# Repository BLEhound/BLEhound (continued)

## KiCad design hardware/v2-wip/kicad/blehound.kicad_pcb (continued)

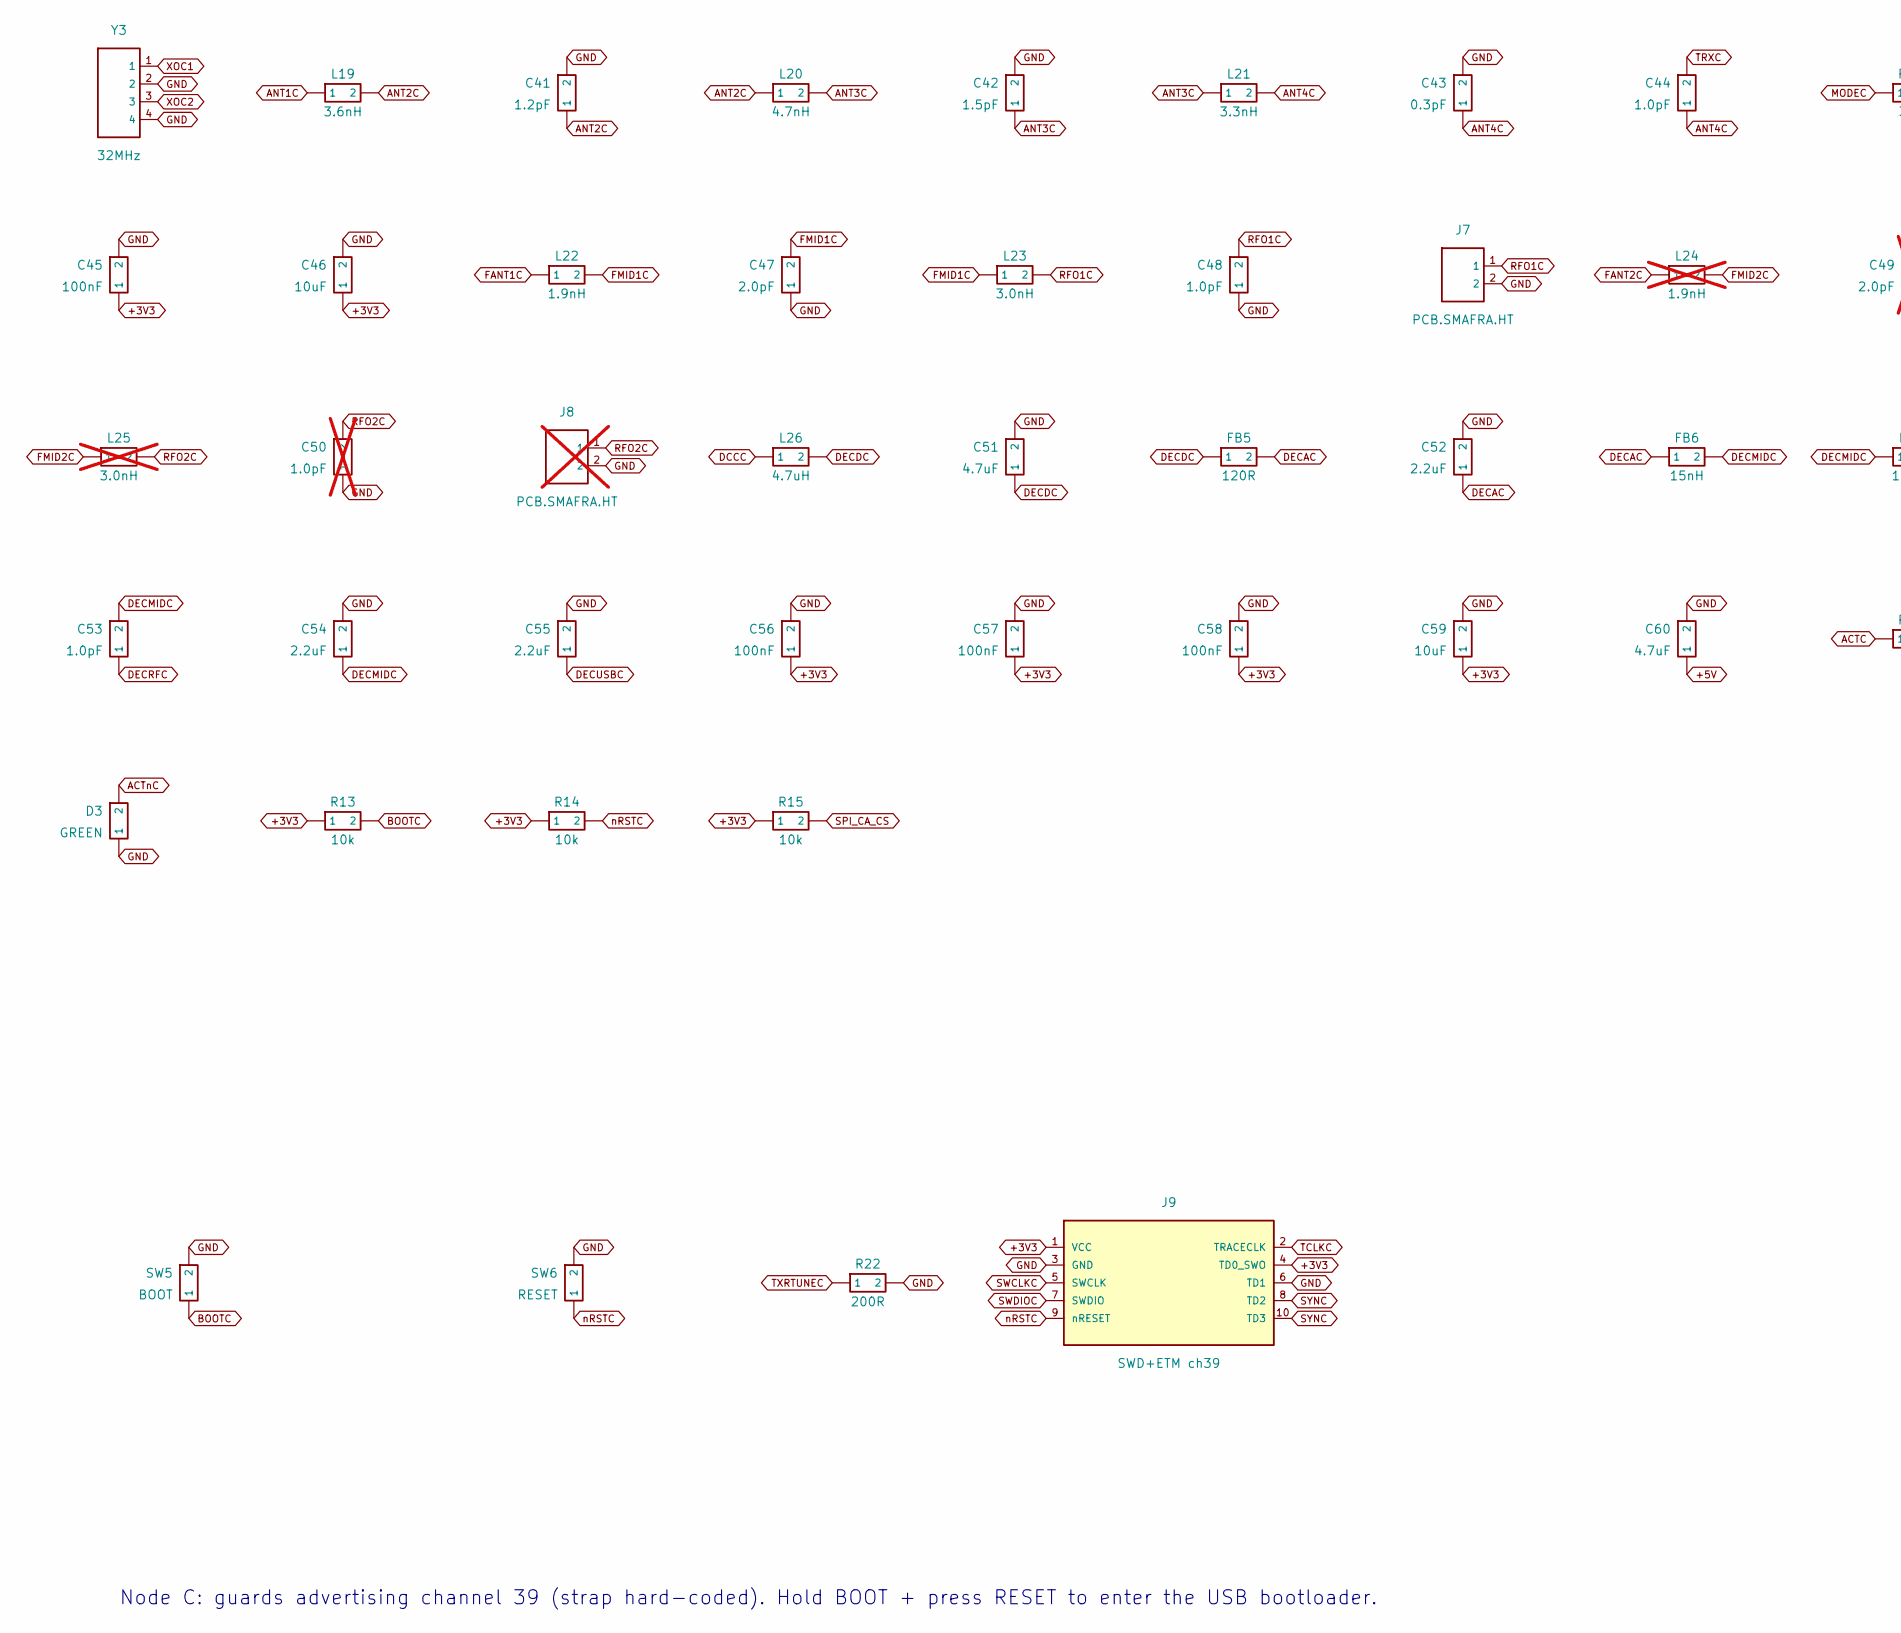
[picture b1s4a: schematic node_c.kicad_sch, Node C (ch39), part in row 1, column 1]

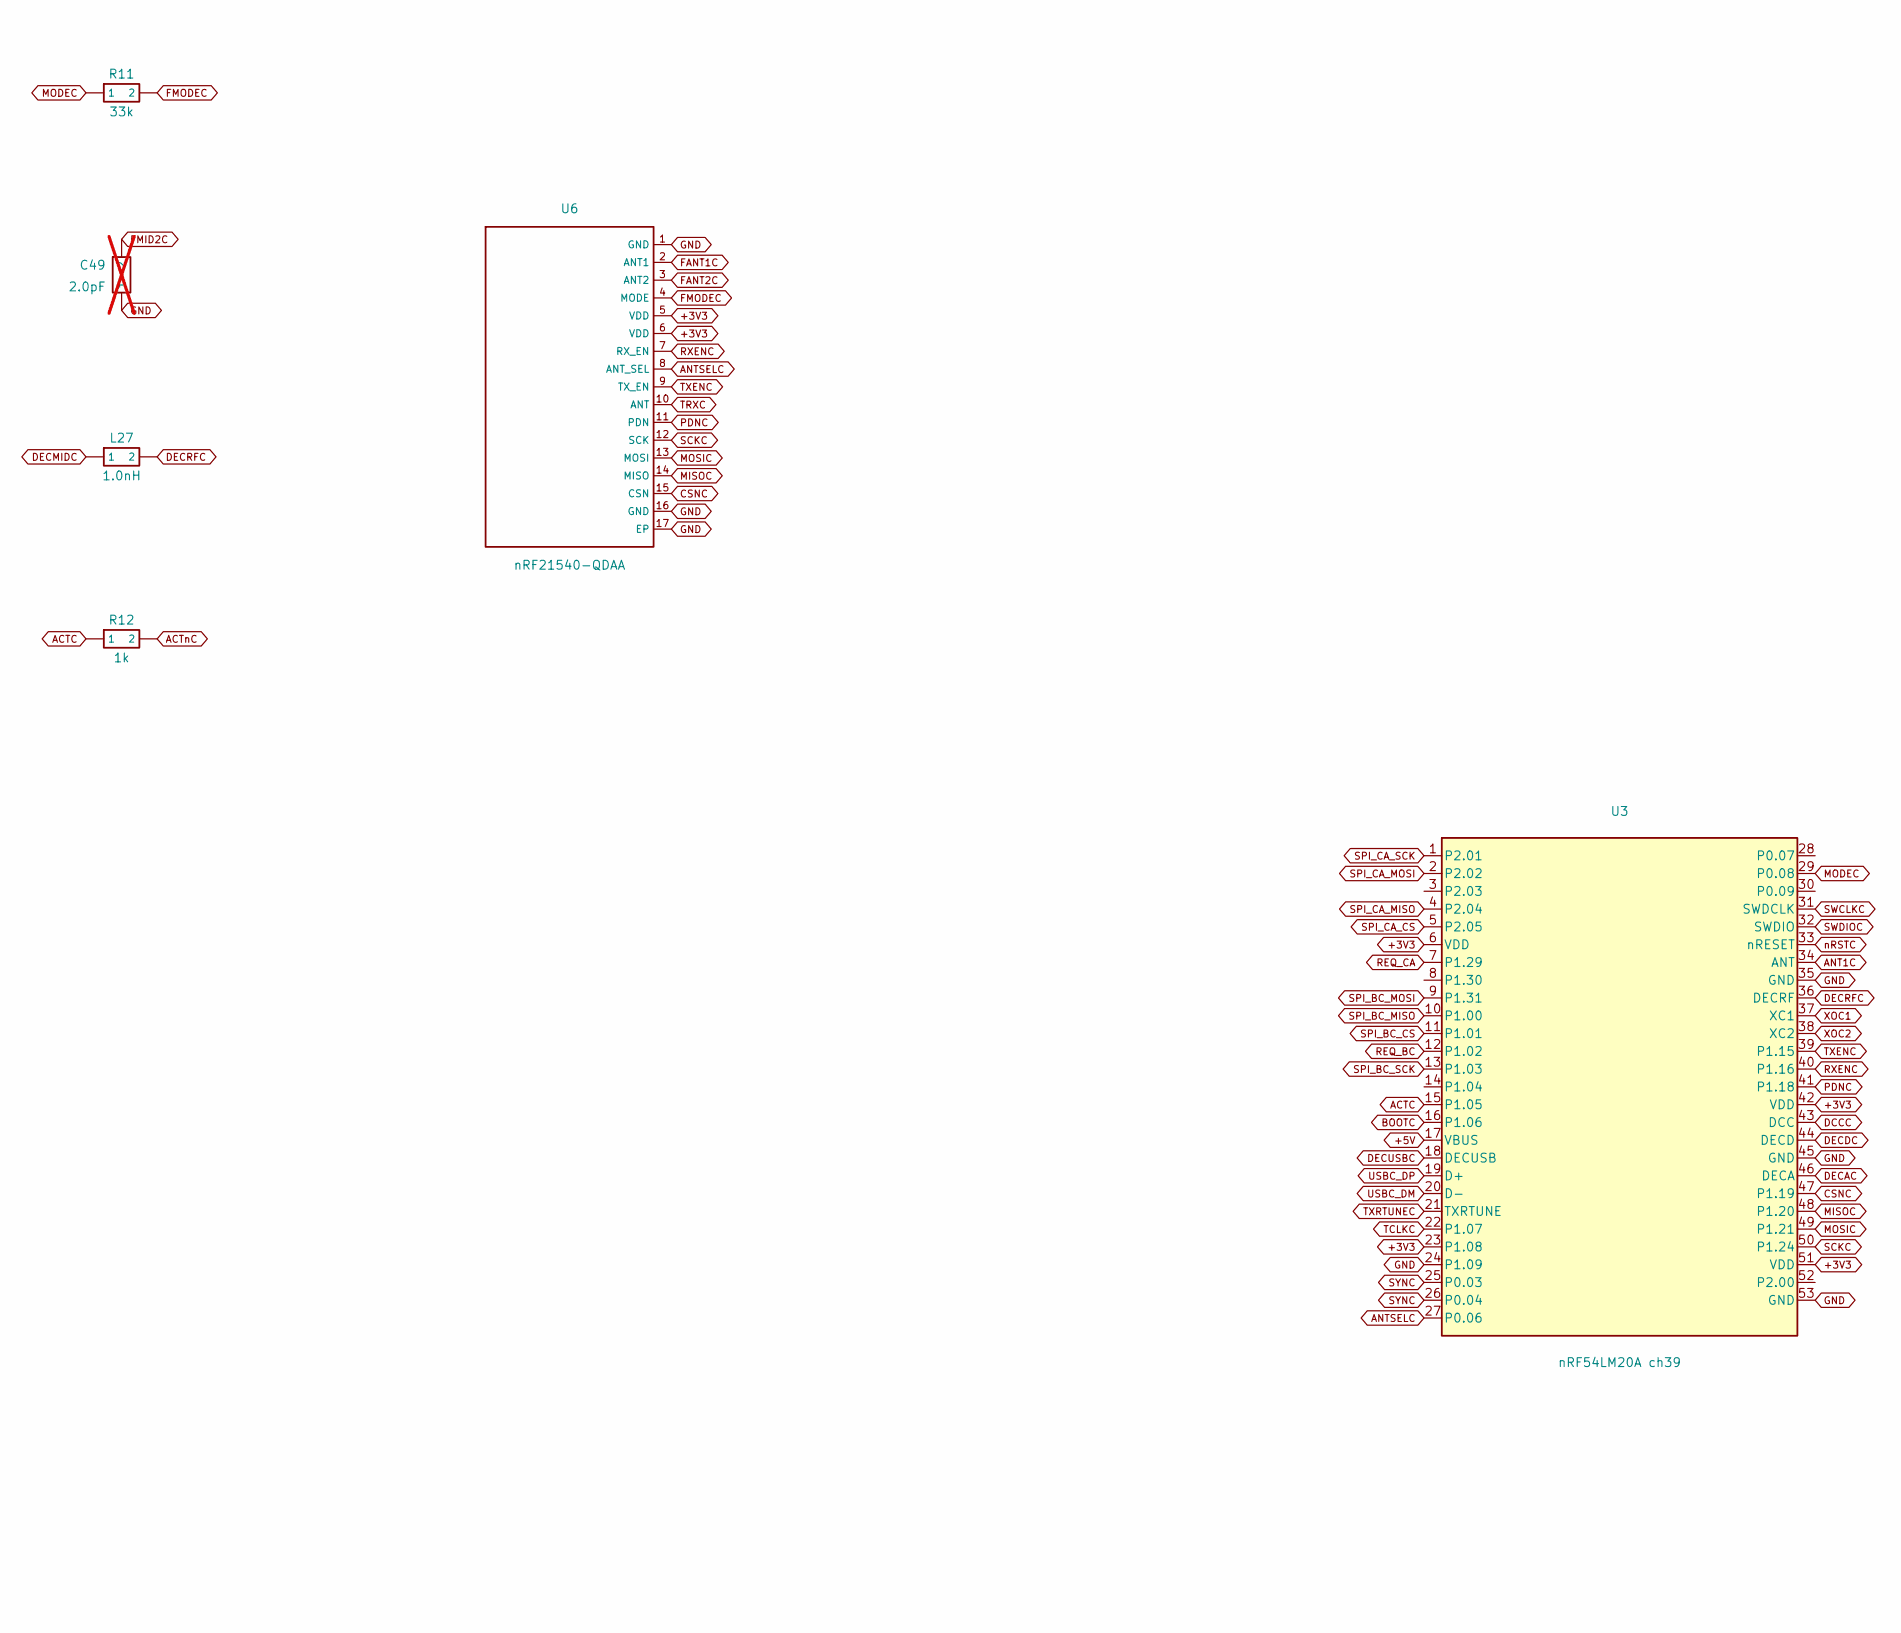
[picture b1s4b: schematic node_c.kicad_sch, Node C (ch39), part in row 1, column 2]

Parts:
C41: 1.2pF; DK_C_0201_0603Metric
C42: 1.5pF; DK_C_0201_0603Metric
C43: 0.3pF; DK_C_0201_0603Metric
C44, C48, C53: 1.0pF; DK_C_0201_0603Metric
C45: 100nF; DK_C_0201_0603Metric
C46: 10uF; DK_C_0603_1608Metric
C47: 2.0pF; DK_C_0201_0603Metric
C49: 2.0pF; DK_C_0201_0603Metric; not fitted
C50: 1.0pF; DK_C_0201_0603Metric; not fitted
C51: 4.7uF; DK_C_0201_0603Metric
C52, C54, C55: 2.2uF; DK_C_0201_0603Metric
C56, C57, C58: 100nF; C_0402_1005Metric
C59: 10uF; C_0603_1608Metric
C60: 4.7uF; C_0603_1608Metric
D3: GREEN; LED_0603_1608Metric
FB5: 120R; DK_L_0201_0603Metric
FB6: 15nH; DK_L_0201_0603Metric
J7: PCB.SMAFRA.HT; SMA_RA_TH_PCBSMAFRA_HT
J8: PCB.SMAFRA.HT; SMA_RA_TH_PCBSMAFRA_HT; not fitted
J9: SWD+ETM ch39; PinHeader_2x05_P2.54mm_Vertical
L19: 3.6nH; DK_L_0201_0603Metric
L20: 4.7nH; DK_L_0201_0603Metric
L21: 3.3nH; DK_L_0201_0603Metric
L22: 1.9nH; DK_L_0201_0603Metric
L23: 3.0nH; DK_L_0201_0603Metric
L24: 1.9nH; DK_L_0201_0603Metric; not fitted
L25: 3.0nH; DK_L_0201_0603Metric; not fitted
L26: 4.7uH; DK_L_0603_1608Metric
L27: 1.0nH; DK_L_0201_0603Metric
R11: 33k; DK_R_0201_0603Metric
R12: 1k; R_0402_1005Metric
R13, R14, R15: 10k; R_0402_1005Metric
R22: 200R; R_0402_1005Metric
SW5: BOOT; SW_SPST_SKQG_WithoutStem
SW6: RESET; SW_SPST_SKQG_WithoutStem
U3: nRF54LM20A ch39; nRF54LM20A_QFN52_6x6mm_P0.4mm_EP4.7x4.7mm
U6: nRF21540-QDAA; nRF21540_QFN16_4x4mm_P0.65mm_EP2.65
Y3: 32MHz; DK_Crystal_32MHz

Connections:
+3V3: C45.1, C46.1, C56.1, C57.1, C58.1, C59.1, J9.1 (VCC), J9.4 (TD0_SWO), R13.1, R14.1, R15.1, U3.6 (VDD), U3.23 (P1.08), U3.42 (VDD), U3.51 (VDD), U6.5 (VDD), U6.6 (VDD); also elsewhere on the board
+5V: C60.1, U3.17 (VBUS); also elsewhere on the board
ACTC: R12.1, U3.15 (P1.05)
ACTnC: D3.2, R12.2
ANT1C: L19.1, U3.34 (ANT)
ANT2C: C41.1, L19.2, L20.1
ANT3C: C42.1, L20.2, L21.1
ANT4C: C43.1, C44.1, L21.2
ANTSELC: U3.27 (P0.06), U6.8 (ANT_SEL)
BOOTC: R13.2, SW5.1, U3.16 (P1.06)
CSNC: U3.47 (P1.19), U6.15 (CSN)
DCCC: L26.1, U3.43 (DCC)
DECAC: C52.1, FB5.2, FB6.1, U3.46 (DECA)
DECDC: C51.1, FB5.1, L26.2, U3.44 (DECD)
DECMIDC: C53.2, C54.1, FB6.2, L27.1
DECRFC: C53.1, L27.2, U3.36 (DECRF)
DECUSBC: C55.1, U3.18 (DECUSB)
FANT1C: L22.1, U6.2 (ANT1)
FANT2C: L24.1, U6.3 (ANT2)
FMID1C: C47.2, L22.2, L23.1
FMID2C: C49.2, L24.2, L25.1
FMODEC: R11.2, U6.4 (MODE)
GND: C41.2, C42.2, C43.2, C45.2, C46.2, C47.1, C48.1, C49.1, C50.1, C51.2, C52.2, C54.2, C55.2, C56.2, C57.2, C58.2, C59.2, C60.2, D3.1, J7.2, J8.2, J9.3 (GND), J9.6 (TD1), R22.2, SW5.2, SW6.2, U3.24 (P1.09), U3.35 (GND), U3.45 (GND), U3.53 (GND), U6.1 (GND), U6.16 (GND), U6.17 (EP), Y3.2, Y3.4; also elsewhere on the board
MISOC: U3.48 (P1.20), U6.14 (MISO)
MODEC: R11.1, U3.29 (P0.08)
MOSIC: U3.49 (P1.21), U6.13 (MOSI)
PDNC: U3.41 (P1.18), U6.11 (PDN)
REQ_BC: U3.12 (P1.02); also elsewhere on the board
REQ_CA: U3.7 (P1.29); also elsewhere on the board
RFO1C: C48.2, J7.1, L23.2
RFO2C: C50.2, J8.1, L25.2
RXENC: U3.40 (P1.16), U6.7 (RX_EN)
SCKC: U3.50 (P1.24), U6.12 (SCK)
SPI_BC_CS: U3.11 (P1.01); also elsewhere on the board
SPI_BC_MISO: U3.10 (P1.00); also elsewhere on the board
SPI_BC_MOSI: U3.9 (P1.31); also elsewhere on the board
SPI_BC_SCK: U3.13 (P1.03); also elsewhere on the board
SPI_CA_CS: R15.2, U3.5 (P2.05); also elsewhere on the board
SPI_CA_MISO: U3.4 (P2.04); also elsewhere on the board
SPI_CA_MOSI: U3.2 (P2.02); also elsewhere on the board
SPI_CA_SCK: U3.1 (P2.01); also elsewhere on the board
SWCLKC: J9.5 (SWCLK), U3.31 (SWDCLK)
SWDIOC: J9.7 (SWDIO), U3.32 (SWDIO)
SYNC: J9.8 (TD2), J9.10 (TD3), U3.25 (P0.03), U3.26 (P0.04); also elsewhere on the board
TCLKC: J9.2 (TRACECLK), U3.22 (P1.07)
TRXC: C44.2, U6.10 (ANT)
TXENC: U3.39 (P1.15), U6.9 (TX_EN)
TXRTUNEC: R22.1, U3.21 (TXRTUNE)
USBC_DM: U3.20 (D-); also elsewhere on the board
USBC_DP: U3.19 (D+); also elsewhere on the board
XOC1: U3.37 (XC1), Y3.1
XOC2: U3.38 (XC2), Y3.3
nRSTC: J9.9 (nRESET), R14.2, SW6.1, U3.33 (nRESET)

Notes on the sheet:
Node C: guards advertising channel 39 (strap hard-coded). Hold BOOT + press RESET to enter the USB bootloader.

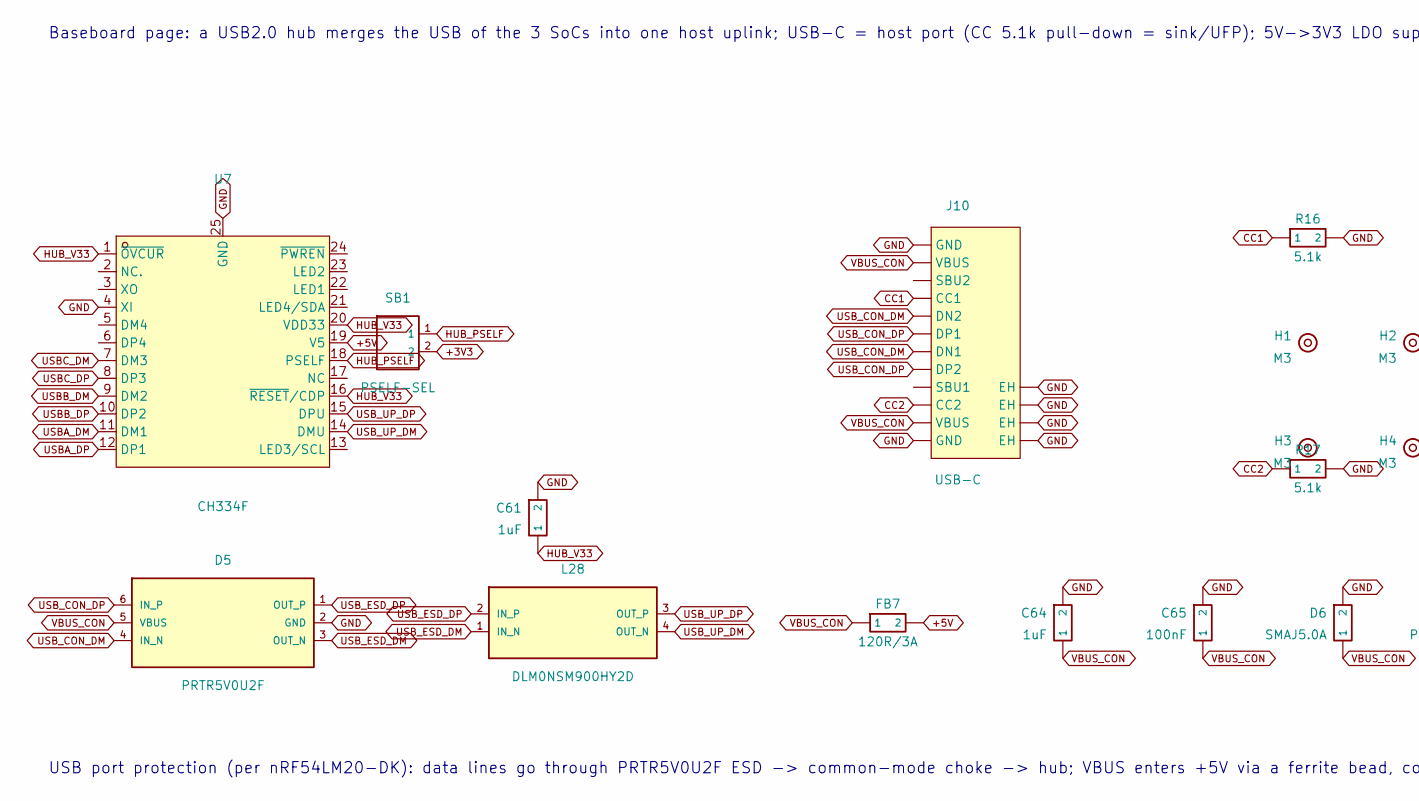
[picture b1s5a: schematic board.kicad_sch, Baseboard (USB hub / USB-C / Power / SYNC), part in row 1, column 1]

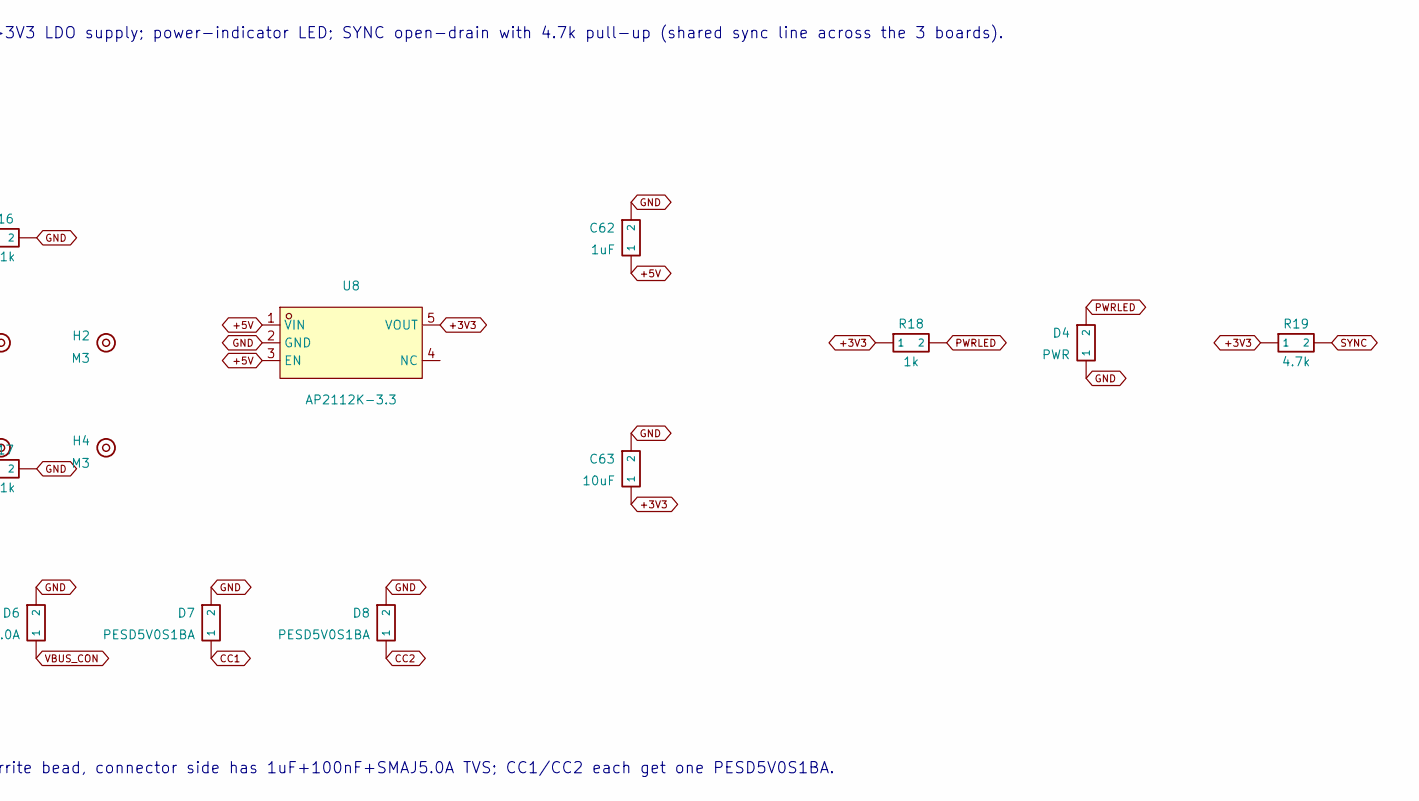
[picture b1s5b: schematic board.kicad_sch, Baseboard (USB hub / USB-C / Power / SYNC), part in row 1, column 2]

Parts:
C61: 1uF; C_0402_1005Metric
C62, C64: 1uF; C_0603_1608Metric
C63: 10uF; C_0603_1608Metric
C65: 100nF; C_0402_1005Metric
D4: PWR; LED_0603_1608Metric
D5: PRTR5V0U2F; SON50P100X50-6N
D6: SMAJ5.0A; D_SMA
D7, D8: PESD5V0S1BA; D_SOD-323
FB7: 120R/3A; INDC1608X06L
H1, H2, H3, H4: M3; MountingHole_3.2mm_M3
J10: USB-C; USB-C_SMD-TYPE-C-31-M-12_1
L28: DLM0NSM900HY2D; CMC0806X05N
R16, R17: 5.1k; R_0402_1005Metric
R18: 1k; R_0402_1005Metric
R19: 4.7k; R_0402_1005Metric
SB1: PSELF-SEL; SolderBridge_Nordic_Bridged
U7: CH334F; QFN-24_L4.0-W4.0-P0.50-BL-EP2.8
U8: AP2112K-3.3; SOT-25-5_L2.9-W1.6-P0.95-LS2.8-BL

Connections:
+3V3: C63.1, R18.1, R19.1, SB1.2, U8.5 (VOUT); also elsewhere on the board
+5V: C62.1, FB7.2, U7.19 (V5), U8.1 (VIN), U8.3 (EN); also elsewhere on the board
CC1: D7.1, J10.A5 (CC1), R16.1
CC2: D8.1, J10.B5 (CC2), R17.1
GND: C61.2, C62.2, C63.2, C64.2, C65.2, D4.1, D5.2 (GND), D6.2, D7.2, D8.2, J10.1 (EH), J10.2 (EH), J10.3 (EH), J10.4 (EH), J10.A1B12 (GND), J10.B1A12 (GND), R16.2, R17.2, U7.4 (XI), U7.25 (GND), U8.2 (GND); also elsewhere on the board
HUB_PSELF: SB1.1, U7.18 (PSELF)
HUB_V33: C61.1, U7.1 (~OVCUR), U7.16 (~RESET/CDP), U7.20 (VDD33)
PWRLED: D4.2, R18.2
SYNC: R19.2; also elsewhere on the board
USBA_DM: U7.11 (DM1); also elsewhere on the board
USBA_DP: U7.12 (DP1); also elsewhere on the board
USBB_DM: U7.9 (DM2); also elsewhere on the board
USBB_DP: U7.10 (DP2); also elsewhere on the board
USBC_DM: U7.7 (DM3); also elsewhere on the board
USBC_DP: U7.8 (DP3); also elsewhere on the board
USB_CON_DM: D5.4 (IN_N), J10.A7 (DN1), J10.B7 (DN2)
USB_CON_DP: D5.6 (IN_P), J10.A6 (DP1), J10.B6 (DP2)
USB_ESD_DM: D5.3 (OUT_N), L28.1 (IN_N)
USB_ESD_DP: D5.1 (OUT_P), L28.2 (IN_P)
USB_UP_DM: L28.4 (OUT_N), U7.14 (DMU)
USB_UP_DP: L28.3 (OUT_P), U7.15 (DPU)
VBUS_CON: C64.1, C65.1, D5.5 (VBUS), D6.1, FB7.1, J10.A4B9 (VBUS), J10.B4A9 (VBUS)

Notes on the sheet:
Baseboard page: a USB2.0 hub merges the USB of the 3 SoCs into one host uplink; USB-C = host port (CC 5.1k pull-down = sink/UFP); 5V->3V3 LDO supply; power-indicator LED; SYNC open-drain with 4.7k pull-up (shared sync line across the 3 boards).
USB port protection (per nRF54LM20-DK): data lines go through PRTR5V0U2F ESD -> common-mode choke -> hub; VBUS enters +5V via a ferrite bead, connector side has 1uF+100nF+SMAJ5.0A TVS; CC1/CC2 each get one PESD5V0S1BA.

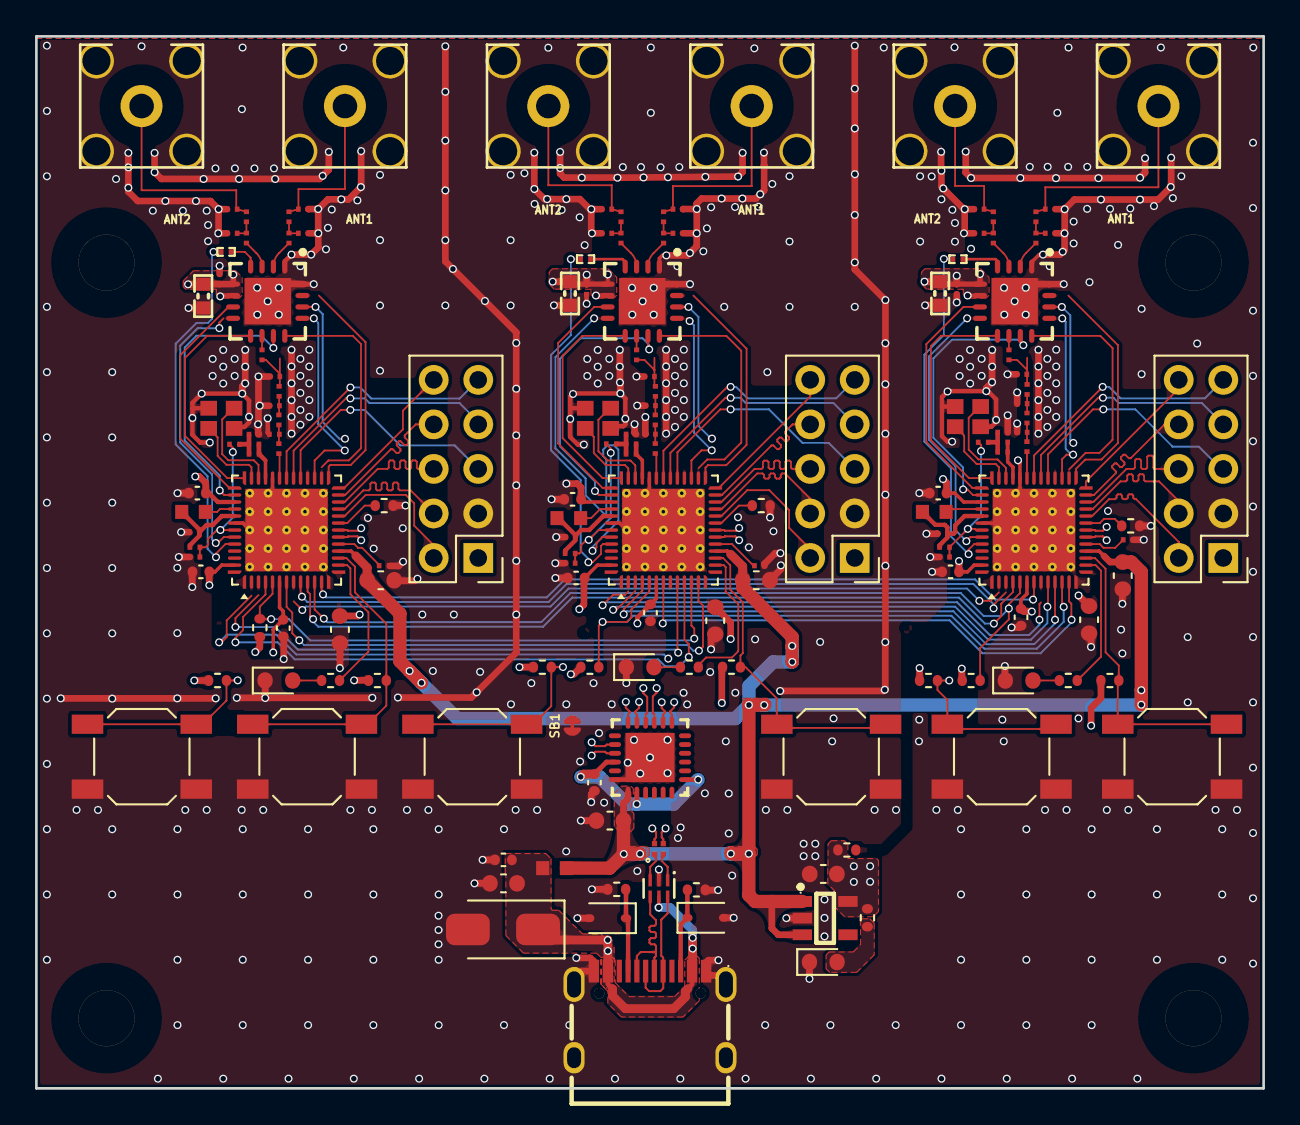
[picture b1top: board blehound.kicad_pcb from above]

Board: 6 copper layers, 70.0 x 60.0 mm, 162 parts (0 on the bottom side), 148 nets.

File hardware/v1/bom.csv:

"Designator","Value","Footprint","Qty","DNP"
"C1,C21,C41","1.2pF","nRF54LM20A:DK_C_0201_0603Metric","3",""
"C2,C22,C42","1.5pF","nRF54LM20A:DK_C_0201_0603Metric","3",""
"C3,C23,C43","0.3pF","nRF54LM20A:DK_C_0201_0603Metric","3",""
"C4,C8,C13,C24,C28,C33,C44,C48,C53","1.0pF","nRF54LM20A:DK_C_0201_0603Metric","9",""
"C5,C25,C45","100nF","nRF54LM20A:DK_C_0201_0603Metric","3",""
"C6,C26,C46","10uF","nRF54LM20A:DK_C_0402_1005Metric","3",""
"C7,C27,C47","2.0pF","nRF54LM20A:DK_C_0201_0603Metric","3",""
"C9,C29,C49","2.0pF","nRF54LM20A:DK_C_0201_0603Metric","3","DNP"
"C10,C30,C50","1.0pF","nRF54LM20A:DK_C_0201_0603Metric","3","DNP"
"C11,C31,C51","4.7uF","nRF54LM20A:DK_C_0201_0603Metric","3",""
"C12,C14,C15,C32,C34,C35,C52,C54,C55","2.2uF","nRF54LM20A:DK_C_0201_0603Metric","9",""
"C16-C18,C36-C38,C56-C58,C65","100nF","Capacitor_SMD:C_0402_1005Metric","10",""
"C19,C39,C59,C63","10uF","Capacitor_SMD:C_0603_1608Metric","4",""
"C20,C40,C60","4.7uF","Capacitor_SMD:C_0603_1608Metric","3",""
"C61","1uF","Capacitor_SMD:C_0402_1005Metric","1",""
"C62,C64","1uF","Capacitor_SMD:C_0603_1608Metric","2",""
"D1-D3","GREEN","LED_SMD:LED_0603_1608Metric","3",""
"D4","PWR","LED_SMD:LED_0603_1608Metric","1",""
"D5","PRTR5V0U2F","nordic:SON50P100X50-6N","1",""
"D6","SMAJ5.0A","Diode_SMD:D_SMA","1",""
"D7,D8","PESD5V0S1BA","Diode_SMD:D_SOD-323","2",""
"FB1,FB3,FB5","120R","nRF54LM20A:DK_L_0201_0603Metric","3",""
"FB2,FB4,FB6","15nH","nRF54LM20A:DK_L_0201_0603Metric","3",""
"FB7","120R/3A","nordic:INDC1608X06L","1",""
"J1,J4,J7","SMA_2081005-1","nordic:SMA_2081005-1","3",""
"J2,J5,J8","SMA_2081005-1","nordic:SMA_2081005-1","3","DNP"
"J3","SWD+ETM ch37","Connector_PinHeader_2.54mm:PinHeader_2x05_P2.54mm_Vertical","1",""
"J6","SWD+ETM ch38","Connector_PinHeader_2.54mm:PinHeader_2x05_P2.54mm_Vertical","1",""
"J9","SWD+ETM ch39","Connector_PinHeader_2.54mm:PinHeader_2x05_P2.54mm_Vertical","1",""
"J10","USB-C","ext:USB-C_SMD-TYPE-C-31-M-12_1","1",""
"L1,L10,L19","3.6nH","nRF54LM20A:DK_L_0201_0603Metric","3",""
"L2,L11,L20","4.7nH","nRF54LM20A:DK_L_0201_0603Metric","3",""
"L3,L12,L21","3.3nH","nRF54LM20A:DK_L_0201_0603Metric","3",""
"L4,L13,L22","1.9nH","nRF54LM20A:DK_L_0201_0603Metric","3",""
"L5,L14,L23","3.0nH","nRF54LM20A:DK_L_0201_0603Metric","3",""
"L6,L15,L24","1.9nH","nRF54LM20A:DK_L_0201_0603Metric","3","DNP"
"L7,L16,L25","3.0nH","nRF54LM20A:DK_L_0201_0603Metric","3","DNP"
"L8,L17,L26","4.7uH","nRF54LM20A:DK_L_0603_1608Metric","3",""
"L9,L18,L27","1.0nH","nRF54LM20A:DK_L_0201_0603Metric","3",""
"L28","DLM0NSM900HY2D","nordic:CMC0806X05N","1",""
"R1,R6,R11","33k","nRF54LM20A:DK_R_0201_0603Metric","3",""
"R2,R7,R12,R18","1k","Resistor_SMD:R_0402_1005Metric","4",""
"R3-R5,R8-R10,R13-R15","10k","Resistor_SMD:R_0402_1005Metric","9",""
"R16,R17","5.1k","Resistor_SMD:R_0402_1005Metric","2",""
"R19","4.7k","Resistor_SMD:R_0402_1005Metric","1",""
"SW1,SW3,SW5","BOOT","Button_Switch_SMD:SW_SPST_SKQG_WithoutStem","3",""
"SW2,SW4,SW6","RESET","Button_Switch_SMD:SW_SPST_SKQG_WithoutStem","3",""
"U1","nRF54LM20A ch37","nRF54LM20A:BGA98C35P10X10_367X385X86","1",""
"U2","nRF54LM20A ch38","nRF54LM20A:BGA98C35P10X10_367X385X86","1",""
"U3","nRF54LM20A ch39","nRF54LM20A:BGA98C35P10X10_367X385X86","1",""
"U4-U6","nRF21540-QDAA","nRF54LM20A:nRF21540_QFN16_4x4mm_P0.65mm_EP2.65","3",""
"U7","CH334F","ext:QFN-24_L4.0-W4.0-P0.50-BL-EP2.8","1",""
"U8","AP2112K-3.3","ext:SOT-25-5_L2.9-W1.6-P0.95-LS2.8-BL","1",""
"Y1-Y3","32MHz","nRF54LM20A:DK_Crystal_32MHz","3",""
